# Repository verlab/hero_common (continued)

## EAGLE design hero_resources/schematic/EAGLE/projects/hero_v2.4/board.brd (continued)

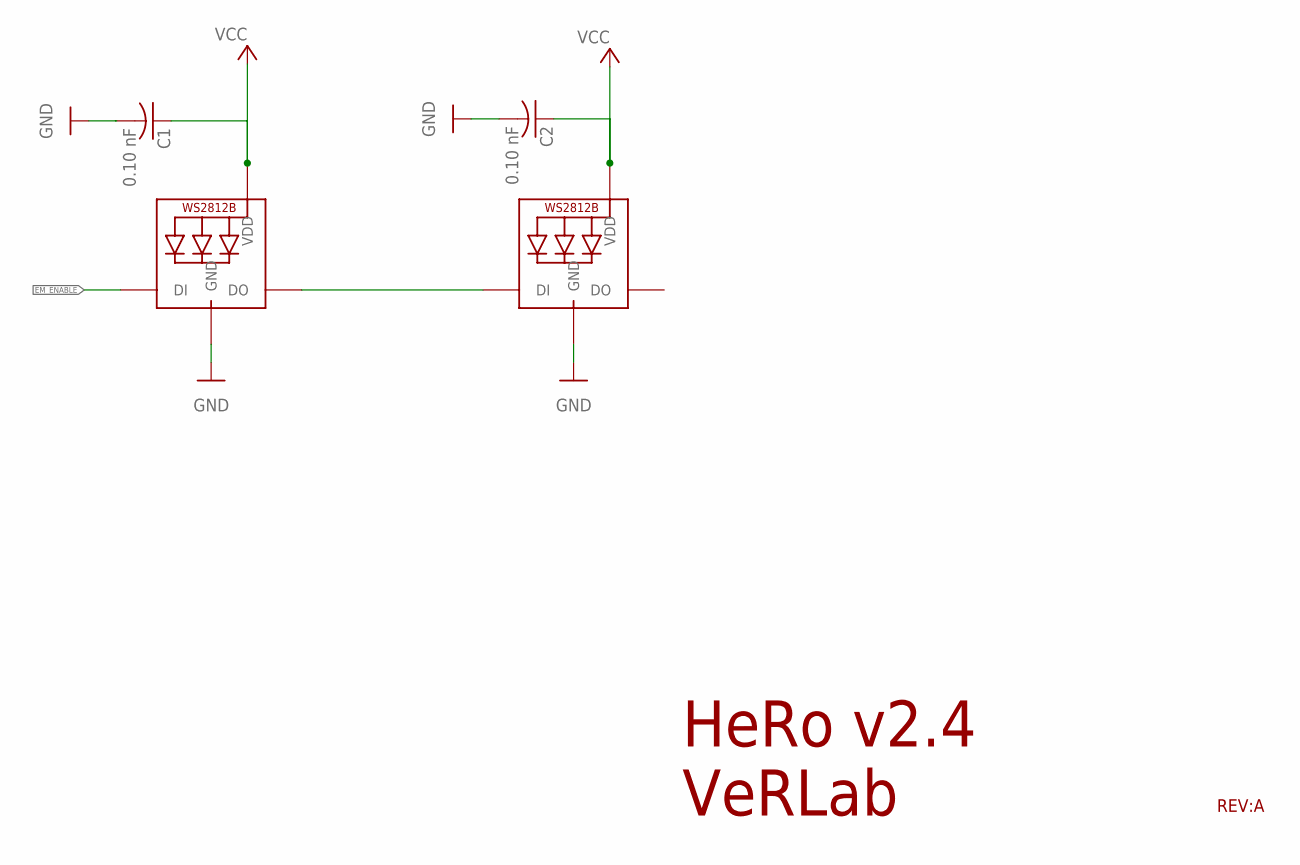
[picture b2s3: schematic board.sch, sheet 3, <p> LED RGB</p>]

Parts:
C1, C2: 0.10 nF; C0603
LED0, LED1: WS2812B5050; WS2812B

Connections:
EM_ENABLE: LED0.4-DIN (DI); also elsewhere on the board
GND: C1.2, C2.2, LED0.3-GND (GND), LED1.3-GND (GND); also elsewhere on the board
VCC: C1.1, C2.1, LED0.1-VDD (VDD), LED1.1-VDD (VDD); also elsewhere on the board
WS_OUT: LED0.2-DOUT (DO), LED1.4-DIN (DI)

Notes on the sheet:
HeRo v2.4 VeRLab
REV:A

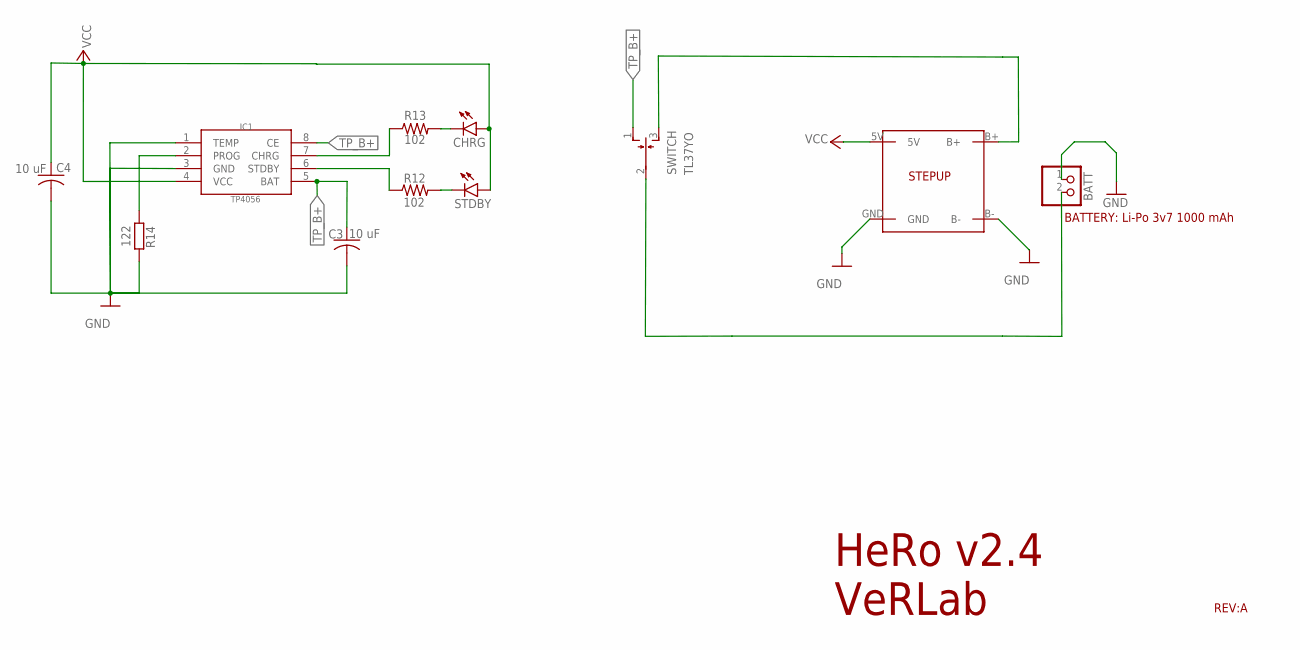
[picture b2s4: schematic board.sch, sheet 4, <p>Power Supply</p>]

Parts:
BATT: PINHD-1X2; 1X02
C3, C4: 10 uF; C0603
CHRG: LEDCHIP-LED0603; CHIP-LED0603
IC1: TP4056; SOP-8
OS1: STEPUP
R12, R13: 102; R0603
R14: 122; R0603
STDBY: LEDCHIP-LED0603; CHIP-LED0603
SWITCH: TL37YO; TL3XYO

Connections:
B+: OS1.B+, SWITCH.3 (S)
CHRG: IC1.7 (CHRG), R13.1
GND: BATT.1, C3.2, C4.2, IC1.1 (TEMP), IC1.3 (GND), OS1.B-, OS1.GND, R14.1; also elsewhere on the board
unnamed: CHRG.A, STDBY.A
unnamed: BATT.2, SWITCH.2
unnamed: CHRG.C, R13.2
unnamed: R12.2, STDBY.C
PROG: IC1.2 (PROG), R14.2
STDBY: IC1.6 (STDBY), R12.1
TP_B+: C3.1, IC1.5 (BAT), IC1.8 (CE), SWITCH.1 (O)
VCC: C4.1, IC1.4 (VCC), OS1.5V; also elsewhere on the board

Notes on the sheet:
HeRo v2.4 VeRLab
BATTERY: Li-Po 3v7 1000 mAh
REV:A

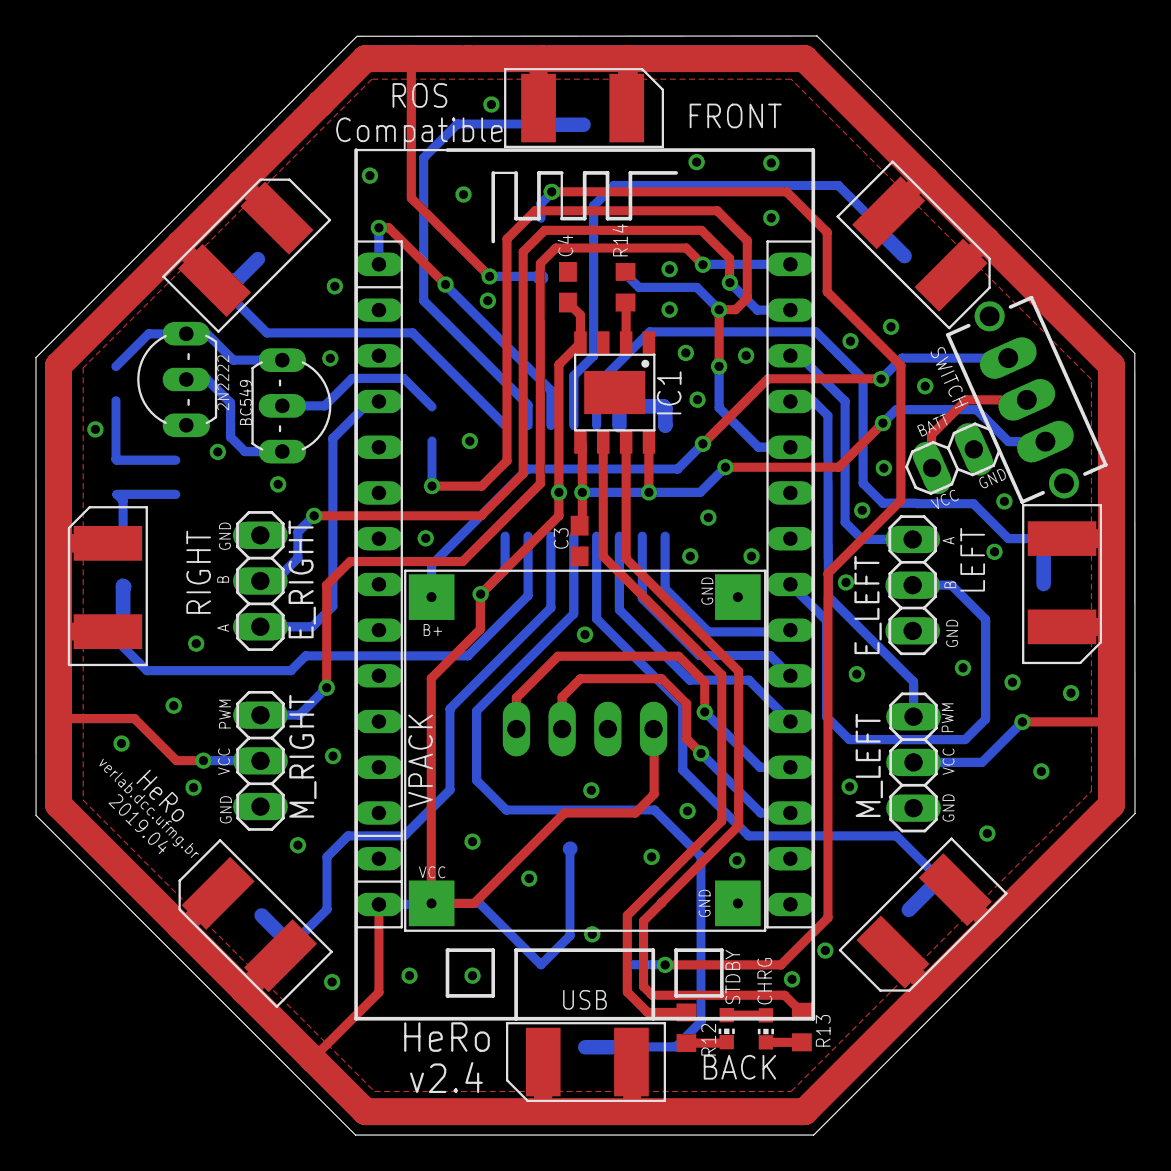
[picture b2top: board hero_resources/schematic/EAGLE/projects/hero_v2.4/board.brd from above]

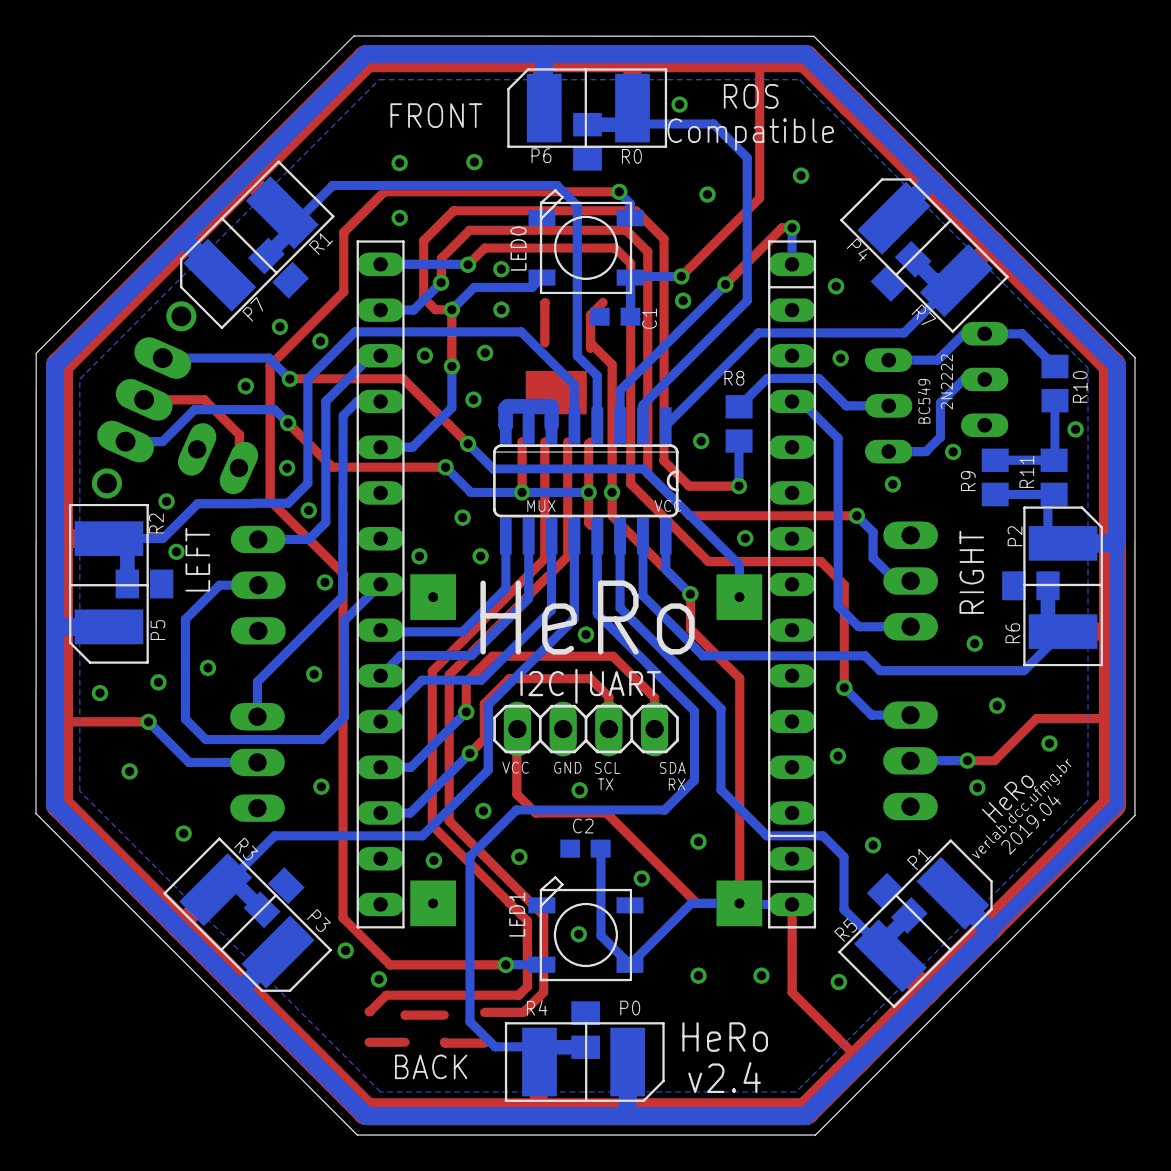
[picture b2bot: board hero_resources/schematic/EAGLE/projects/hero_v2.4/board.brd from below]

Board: 2 copper layers, 61.1 x 61.1 mm, 44 parts (18 on the bottom side), 38 nets.

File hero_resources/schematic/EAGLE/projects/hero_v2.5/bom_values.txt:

Partlist exported from /home/rezeck/EAGLE/projects/hero_v2.5/board.sch at 6/5/19 10:48 AM

Qty Value         Device         Package       Parts                            Description                  SPICEPREFIX
2                 LEDSML0805     SML0805       CHRG, STDBY                      LED                                     
1                 MOSFET-NREFLOW SOT23         IRLML2502                        N-Channel Mosfet                        
1                 PINHD-1X2      1X02          BATT                             PIN HEADER                              
4                 PINHD-1X3      1X03          E_LEFT, E_RIGHT, M_LEFT, M_RIGHT PIN HEADER                              
1                 PINHD-1X4      1X04          I2C|UART                         PIN HEADER                              
1                 STEPUP         STEPUP        OS1                                                                      
8                 TCRT5000       TCRT5000      P0, P1, P2, P3, P4, P5, P6, P7                                           
1   0 R           R-US_R0805     R0805         R9                               RESISTOR, American symbol    R          
2   0.10 nF       C-USC0603      C0603         C1, C2                           CAPACITOR, American symbol              
2   10 uF         C-USC0603      C0603         C3, C4                           CAPACITOR, American symbol              
2   102           R-EU_R0805     R0805         R12, R13                         RESISTOR, European symbol               
1   122           R-EU_R0603     R0603         R14                              RESISTOR, European symbol               
1   18 R          R-US_R0805     R0805         R10                              RESISTOR, American symbol    R          
1   4051D         4051D          SO16          IC2                              8-channel ANALOG MULTIPLEXER            
8   4k7           R-US_M0805     M0805         R0, R1, R2, R3, R4, R5, R6, R7   RESISTOR, American symbol               
1   4k7           R-US_R0805     R0805         R8                               RESISTOR, American symbol    R          
1   ESP12E_DEVKIT ESP12E_DEVKIT  ESP12E_DEVKIT U$1                              ESP12E DEVKIT BOARD                     
1   NM            R-US_R0805     R0805         R11                              RESISTOR, American symbol    R          
1   TL37YO        TL37YO         TL3XYO        SWITCH                           TINY SWITCH MOM OFF MOM                 
1   TP4056        TP4056         SOP-8         IC1                                                           X          
2   WS2812B5050   WS2812B5050    WS2812B       LED0, LED1

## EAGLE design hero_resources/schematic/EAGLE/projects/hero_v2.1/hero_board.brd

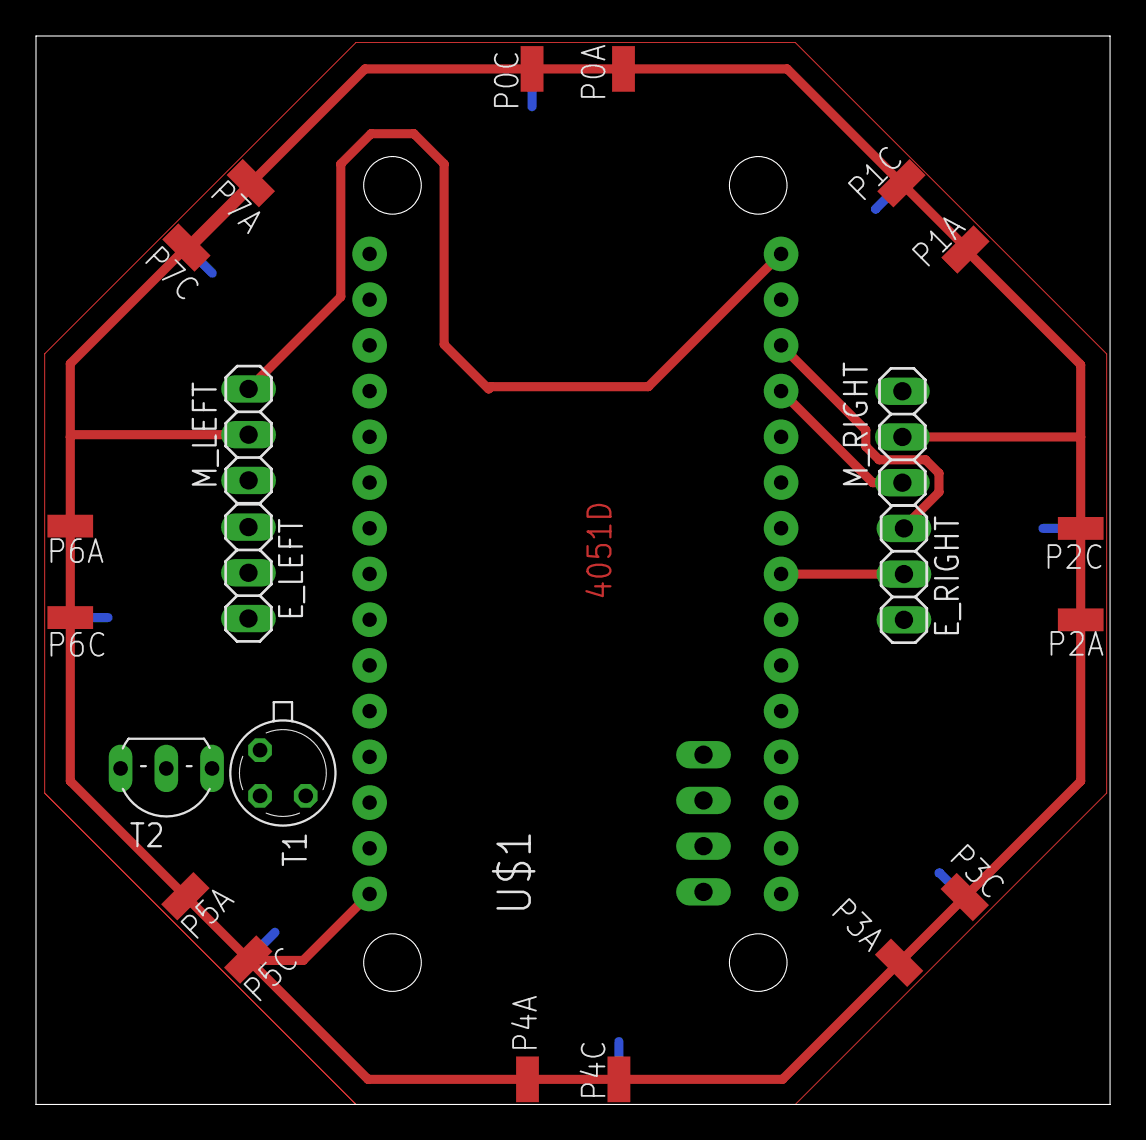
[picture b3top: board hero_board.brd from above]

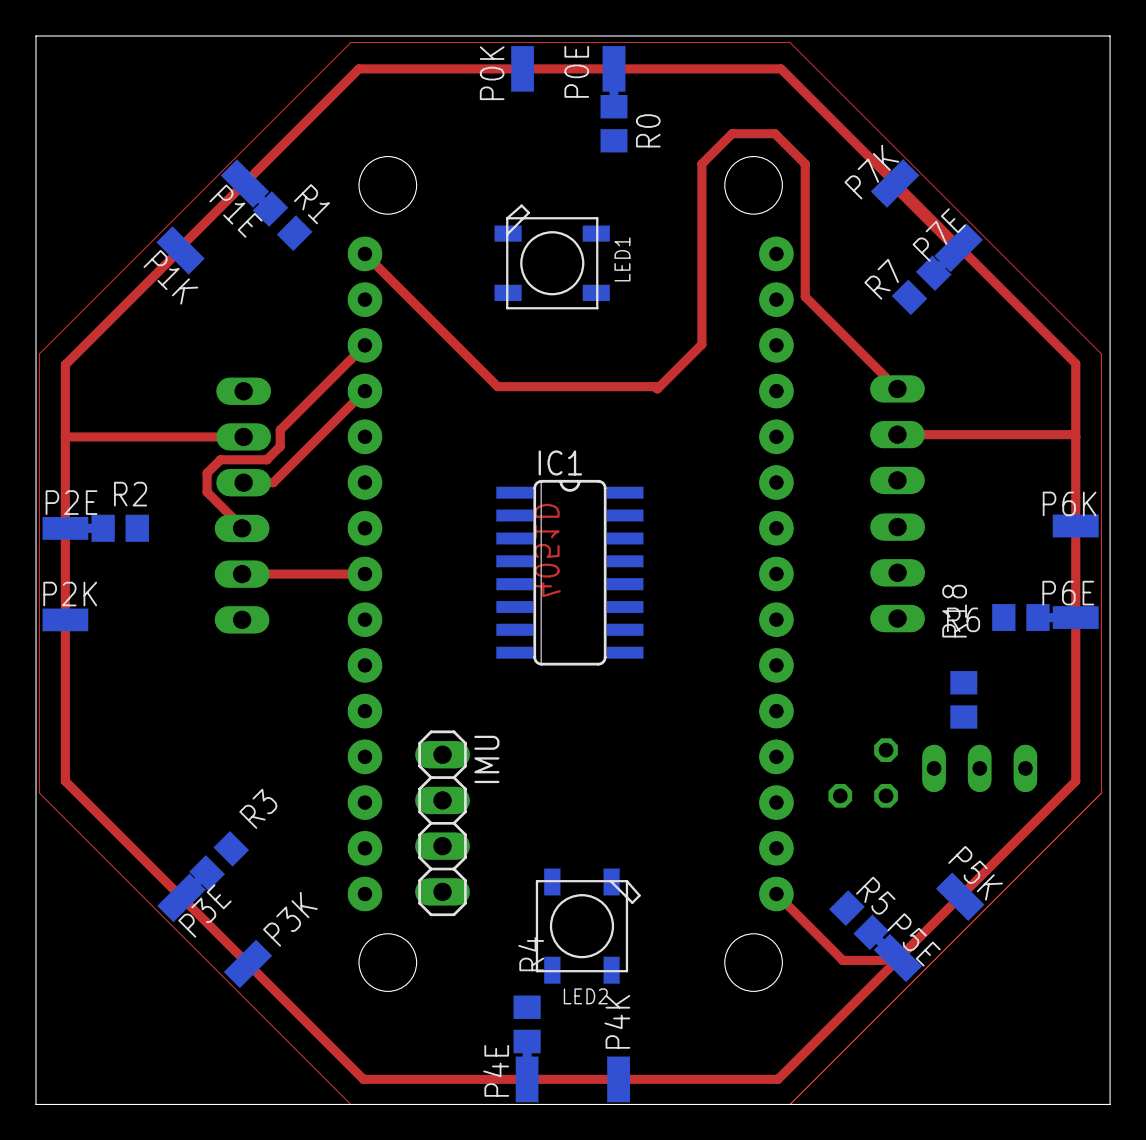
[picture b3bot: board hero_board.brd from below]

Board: 2 copper layers, 59.7 x 59.4 mm, 52 parts (29 on the bottom side), 27 nets.

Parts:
E_LEFT: 1X03
E_RIGHT: 1X03
IC1: 4051D; SO16
IMU: 1X04
LED1, LED2: WS2812B5050; WS2812B
M_LEFT: 1X03
M_RIGHT: 1X03
P0A, P0C, P0E, P0K, P1A, P1C, P1E, P1K, P2A, P2C, P2E, P2K, P3A, P3C, P3E, P3K, P4A, P4C, P4E, P4K, P5A, P5C, P5E, P5K, P6A, P6C, P6E, P6K, P7A, P7C, P7E, P7K: SMD1,27-2,54
R0, R1, R2, R3, R4, R5, R6, R7, R18: R0805
T1: 2N2222; TO18
T2: TO92-CBE
U$1: ESP12E_DEVKIT

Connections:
AD0: IC1.3, U$1.AD0
EM: P0K.1, P1K.1, P2K.1, P3K.1, P4K.1, P5K.1, P6K.1, P7K.1, R18.2
EM_ENABLE: LED1.4-DIN, T2.B, U$1.D4
E_LEFT_A: E_LEFT.3, U$1.SD3
E_LEFT_B: E_LEFT.2, U$1.D1
E_RIGHT_A: E_RIGHT.3, U$1.D2
E_RIGHT_B: E_RIGHT.2, U$1.D5
GND: E_LEFT.1, E_RIGHT.1, IC1.6, IC1.8, IMU.3, LED1.3-GND, LED2.3-GND, M_LEFT.1, M_RIGHT.1, R0.2, R1.2, R2.2, R3.2, R4.2, R5.2, R6.2, R7.2, T1.1, U$1.GND@1
MUX_A: IC1.11, U$1.D6
MUX_B: IC1.10, U$1.D7
MUX_C: IC1.9, U$1.D8
MUX_X0: IC1.13, P0E.1, R0.1
MUX_X1: IC1.14, P1E.1, R1.1
MUX_X2: IC1.15, P2E.1, R2.1
MUX_X3: IC1.12, P3E.1, R3.1
MUX_X4: IC1.1, P4E.1, R4.1
MUX_X5: IC1.5, P5E.1, R5.1
MUX_X6: IC1.2, P6E.1, R6.1
MUX_X7: IC1.4, P7E.1, R7.1
M_LEFT_PWM: M_LEFT.3, U$1.D0
M_RIGHT_PWM: M_RIGHT.3, U$1.D3
unnamed: T1.2, T2.E
unnamed: R18.1, T1.3, T2.C
unnamed: LED1.2-DOUT, LED2.4-DIN
SCL_TX: IMU.2, U$1.TX
SDA_RX: IMU.1, U$1.RX
VCC: IC1.16, IMU.4, LED1.1-VDD, LED2.1-VDD, M_LEFT.2, M_RIGHT.2, P0A.1, P0C.1, P1A.1, P1C.1, P2A.1, P2C.1, P3A.1, P3C.1, P4A.1, P4C.1, P5A.1, P5C.1, P6A.1, P6C.1, P7A.1, P7C.1, U$1.VIN

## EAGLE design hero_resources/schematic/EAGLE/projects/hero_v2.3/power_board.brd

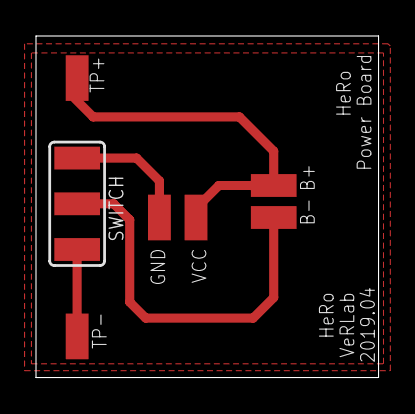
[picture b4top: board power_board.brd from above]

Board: 2 copper layers, 19.0 x 19.0 mm, 7 parts (0 on the bottom side), 4 nets.

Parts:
B+: SMD1,27-2,54
B-: SMD1,27-2,54
GND: SMD1,27-2,54
SWITCH: SJ_2W
TP+: SMD1,27-2,54
TP-: SMD1,27-2,54
VCC: SMD1,27-2,54

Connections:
unnamed: B-.1, SWITCH.2
unnamed: GND.1, SWITCH.1
unnamed: B+.1, TP+.1, VCC.1
unnamed: SWITCH.3, TP-.1

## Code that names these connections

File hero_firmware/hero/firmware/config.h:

/*
 ************************************************************************
 *  H E R O   F I R M W A R E
 ************************************************************************
 *
 * Paulo Rezeck <rezeck@dcc.ufmg.br>
 * Mauricio Ferrari <mauferrari@dcc.ufmg.br>
 * Hector Azpurua <hectorxxx@gmail.com>
 * 
 * HeRo Project
 * Computer Vision and Robotics Lab
 * Federal University of Minas Gerais - Brazil
 ************************************************************************/

#ifndef __CONFIG_H__
#define __CONFIG_H__

#define DEBUG 1


/* WIFI Config */
#define IP_A 10
#define IP_B 42
#define IP_C 0
#define IP_D 1
#define WIFI_SSID "epuck_net" // network name
#define WIFI_PASSWD "epuck_9895" // network password
#define ROS_MASTER_PORT 11411


/* Robot Params */
#define WHEEL_DIAMETER 4.955     /* Wheel diameter in cm. */
#define WHEEL_SEPARATION 6.335   /* Separation between wheels (cm) */
#define WHEEL_DISTANCE 0.06335   /* Distance between wheels in meters (axis length) */
#define WHEEL_CIRCUMFERENCE ((WHEEL_DIAMETER * M_PI)/100.0)  /* Wheel circumference (meters). */
#define MOT_STEP_DIST (WHEEL_CIRCUMFERENCE/288.0)  /* Distance for each motor step (meters); 
                                                      a complete turn is 288 steps (0.000535598 meters per step (m/steps)).

/* IO */
#define ENC_A_LEFT 14 // D2
#define ENC_B_LEFT 4 // D5
#define ENC_A_RIGHT 10 // SD3
#define ENC_B_RIGHT 5 // D1
#define MOTOR_RIGHT 16 // D3
#define MOTOR_LEFT 0 // D0
#define MUX_A 15 // D8
#define MUX_B 13 // D7
#define MUX_C 12 // D6
#define MUX_EN 2 // D4
#define I2C_SDA 3 // RX
#define I2C_SCL 1 // TX


/* WS2812b */
#define COLOR_SATURATION 255

/* MUX IR Control */
/* Analog Multiplexer 4051 */
//const int real_pos[8] = {0,1,2,5,6,7,4,3};
const int real_pos[8] = {0, 1, 2, 7, 3, 6, 4, 5};
// 0, 1, 2, 4, 6, 7, 5, 3

/* Control */
#define ENCODER_SPEED_GAIN 0.06
#define DEFAULT_KP 1200
#define DEFAULT_KI 7.5
#define DEFAULT_KD 3.5

#define MAX_BUFFER_SIZE 100

#endif  // ___CONFIG_H__

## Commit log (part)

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2017-03-08 Implemented differential control
2017-03-08 Renamed some files and disable robot to publish they ids
2017-03-09 Updated servo motor neutral position
2017-03-18 Added some info on README
2017-03-18 added cad file of robot
2017-03-18 fix line
2017-03-20 Rename launch and change neutral position of the wheels.
2017-03-20 Update servo neutral position
2017-03-20 Created teleop launch to control via keyboard the robots
2017-03-20 Adjust to use microseconds write on servo
2017-03-22 Implemented sender mode on robots
2017-03-23 Remove submodule entry
2017-03-23 Added RF24 library modified.
2017-03-23 Implement mode to automatic find the enable robots in environment.
2017-03-24 Implement mode to (simutaneous) receive data from Sensors and control the robot.
2017-04-05 Set all read pipes with the same address
2017-04-05 Set teleop launch to control a specific robot
2017-04-13 Create WifiHardware to comunicate via wifi with ros using nodemcu device
2017-04-14 Create a new messages types and implement robot firmware based on ROS
2017-04-17 Removed sensitive data from file
2017-05-26 Add IR sensor
2017-05-27 Simplified arduino code, added twist messages, simple config in main cpp file
2017-05-27 added new control algo simplified some functions, need some more testing
2017-05-30 reverted old control algo
2017-05-30 added camera and tracker launch file
2017-05-30 added camera parameters in file
2017-05-30 Added calibration file from arena
2017-05-30 Added markers folder, and tracker script to make the robot follow a goal marker.
2017-05-30 updated track launch file
2017-05-30 updated tracker software and a simple random walker for the nodemcu firmware
2017-05-31 updated camera launch
2017-06-01 added serial node, modified to accept different ports
2017-06-02 Added common markers
2017-06-05 Add into firmware the parameter of the second robot, added potential field control.
2017-06-05 Added tracker, firmware parameters, markers
2017-06-07 Update README.md
    Describing HeRo setup.
2017-06-07 Rename package
2018-04-17 added nodemcu firmware with a friendly EEPROM editor
2018-05-04 Added 3d printer parts
2018-05-04 Added nodemcu and jst pin 3d model
2018-05-04 Added tcrt5000 3d model
2018-08-21 Added new cad model
2018-09-26 Add description and simulation on gazebo
2018-09-27 Added laser and multi hero launch
2018-10-02 Improved collision, inertial and modularization
2018-10-02 Fix laser noise and differential controller plugin
2018-10-02 Added populations cardbox
2018-10-02 Added set of examples to control hero; added blink controller and potential field controller for local navigation.
2018-10-02 Added gazebo images and hero rendered
2018-10-03 Added call for rosserial tcp server into hero bringup; Teleop using keyboard it's also include.
2018-10-05 Added Gazebo ros graph image
2018-10-05 Added some test to hero firmware
2018-10-20 Added support to ar track alvar to provide global pose to HeRo; Not tested yet.
2018-10-24 Update odometry_test
2018-10-24 Added odometry test; hero compare to epuck.
2019-01-15 Added IR, IMU and Encoders tests
2019-01-15 Update firmware with IMU, Encoders, IR and LEDs
2019-01-15 Added cad and board schematic
2019-01-28 Added new 3d model; update tests; refactor sketches
2019-04-17 Remove verbose of gazebo launch and update gazebo world with real time
2019-04-17 Update PCB schematic; Version 2.5 not tested yet.
2019-04-22 Fix battery connector position in board v2.5
2019-04-24 Fix unset interruption mode to the GPIO10; Check if the esp8266 is on DIO Flash mode.
2019-04-24 Fix board v2.5 charge power led to 0805.
2019-04-28 Added new message types for encoder and motor; update setPID service;
2019-04-28 Update firmware to version 2.5; refactored the firmware; added webpage setup wifi; fix encoder read interruption; fix PID parameters
2019-04-28 Added picture resource
2019-06-03 Added builded binary code
2019-06-03 Remove PID library
2019-06-03 Fix PID library
2019-06-05 Added hero v2.5 board BOM
2019-12-12 Fix neopixel test delay
2020-01-17 Added ir and neopixel test; enable rosserial server to fork.
2020-01-17 Fix wifi setup.
2020-01-23 Fix some issues in these test; Add ir and neopixel test
2020-01-25 Added mosfet datasheet
2020-01-29 updating the list of ROS package dependeces
2020-01-29 updating how to install information
2020-01-29 add the arduino IDE download link
2020-01-30 Fix ROS package dependencies; Add hero_firware as ROS package; Add N025P datasheet.
2020-02-08 Update ros library; Update neopixel, ir and motor tests
2021-02-04 Improve gazebo simulation setup; add swarm arena setup;
2021-02-07 Change simulation parameters
2021-07-15 updating 3d model parts
2022-04-13 Major Modifications
2022-04-14 Remove ar-track-alvar dependencies
2022-04-14 remove ar-track dependencies
2022-04-14 Update to use urdf instead xacro -- fix ros noetic version
2022-04-19 Update eagle projects; BOM available
2022-04-19 Update BOM; TP4056 Optional
2022-04-20 Add last CAD model
2022-04-21 Fix castor wheel 3d printer stl
2022-04-21 Fix motor gear 3d printer file
2022-04-26 Set theme jekyll-theme-slate
2022-04-27 Rename _layouts.md to _layouts/defaults.md
2022-04-27 Rename defaults.md to default.html
2022-05-01 Setup new gh-pages
2022-05-03 Delete default.html
    Delete default.html because it was the old home page
2022-05-04 Add feature save launch file name dialog for hero wizard
2022-05-16 Add swtich key datasheet
2022-05-17 Update datasheet links
2022-05-17 Fix Header Responsivity
2022-05-18 Add assembly_table.pdf
2022-05-19 Update Materials
2022-05-25 Add file assembly_materials.pdf
2022-06-13 Created rgbscreen.py
2022-06-14 commit changes
2022-06-14 New pages added
2022-06-14 Fix pcb_order nav-bar
2022-06-15 Update hero_resources
2022-06-15 Major Update
2022-06-16 Add castor wheel and wheel assembly tutorial
2022-06-16 Remove assembly tutorial title
2022-06-16 add rivet to material list
2022-06-16 Update material list
2022-09-07 Adding docker files
2022-09-07 Fix shebang python3
2022-09-07 Fix shebang for python3; Add wizard gui images
2022-09-07 Fix package dependecies list
2022-09-07 Add docker file; fix dependencies list
2022-09-07 Launch ROS1 container
2022-09-07 Launch ROS1 container example
2022-10-09 Update PCB to support MT3608 stepup
2023-01-05 Fix resistors (builtin charge) wrong description
2023-01-05 Fix builtin recharger resistor wrong description #16
2023-01-07 Fix IRAM_ATTR problem with interrupts on ESP8266; Encoder Lib v1.4.3; issue #15
2023-01-07 Fix i2s.h missing issue for NeoPixelBus, esp8266 board > 2.5.0-3.1.0; issue #14
2023-01-07 Update firmware version
2023-01-08 Fix Encoder Lib absence of interrupt on gpio 10
2023-01-08 Fix tf name for laser frame
2023-01-09 Fix MOSFET pinMode reset for IR sensors
2023-02-09 Fix constant parameter
2023-02-09 Fix robot urdf compatibility
2023-02-09 Update robot config params
2023-02-13 Fix rviz config file
2023-02-13 Update firmware config file and fix bug IR sensor
2023-02-13 Add IR calibration script #17
2023-02-13 Add IR Calibration Support 3D printer #17
2023-02-13 Fix xacro urdf remapping #18, thanks @jacobh2299
2023-03-06 Fix incorrectlu battery connector polarity labeled on PCB #19
2023-07-27 Add random walk demo to firmware
2023-07-27 Fix docker launch script image name
2023-07-27 Update range sensor example
2023-08-10 Add IR calibration script
2023-08-10 Fix IR overdriver and signal to meter function
2023-08-10 Update launch file
2023-08-12 Update robot description in launch file
2023-08-12 Fix rosserial flushoutput and add rqt
2023-08-14 Update frame name for compability with noetic
2023-08-14 Add calibration script
2023-08-26 Update docker launch script
2023-08-26 Decrease motor stiffness param
2023-09-02 Update pcb board version
2023-09-02 Update firmware
2023-09-02 Update docker and launch files
2023-09-06 Fix hero gazebo wizard ui size constraint
2023-09-13 Fix the tf part of the launch file generation script
2023-09-14 Update dockerfile
2023-09-20 Add new arena environments and maps
2023-09-20 Add map server for simulated arenas
2023-09-22 Fix map z origin to match with arena floor
2023-09-22 Update hero laser description to match with real robots
2023-09-22 Remove unecessary file
2023-09-23 Fix map undesired rotation param
2023-09-23 Reduce mesh polygon to improve gazebo performance
2023-09-24 Reduce model polygons to increase simulation performance
2023-09-25 Changing from alvartrack to apriltag camera tracker
2023-10-02 Fix unindent typo issue
2023-10-03 Add script to convert tag pose information to robot odometry
2023-10-08 Update camera calibration parameters
2023-10-08 Decrease hero simulation update rate
2023-10-08 Fix unmatching PCB board version 2.7 (issue #22)
2023-10-08 Update pcb_order.md
    Fix link for wrong gerber pcb version
2023-10-16 local planner topics name correction
2023-10-23 Add catkin build tools
2024-02-24 Update hero tracker configuration
2024-02-24 Add tag to pose converter and filter
2024-02-24 Add localization filter and update rviz config
2024-02-24 Add laser enable/disable ros topics
2024-02-24 Update gazebo sim parameters
2024-02-24 Update ros1 docker launch script
2026-05-04 Add initial PlatformIO configuration and web configuration files for HERO firmware
    - Created .gitignore to exclude build artifacts and IDE files.
    - Added platformio.ini for managing project dependencies and build settings.
    - Updated config.h with new versioning and motor ramp parameters.
    - Enhanced IMUSensor and MotorDriver classes for web configuration support.
    - Introduced web_config_embed files for offline web UI.
    - Implemented LEDStatus and WheelEncoder updates for web integration.
2026-05-07 Update firmware version and enhance web configuration
    - Updated FIRMWARE_VERSION to "v3.11" in config.h.
    - Improved comments for proximity sensor calibration indices in config.h.
    - Refactored web configuration HTML for clarity, including renaming tabs and headers for better user experience.
    - Adjusted API telemetry handling in WebConfig.ino to utilize new laser scan slot angle order for IR sensor data processing.
2026-06-11 Enhance motor control initialization and configuration
    - Updated motor pin definitions in config.h for clarity on GPIO usage.
    - Introduced MotorPinsEarlyInit struct in firmware.ino to ensure motor pins are set to LOW before global constructors run.
    - Added drivePinsSafe method in MotorDriver class to safely set motor pins to LOW after detaching servos.
    - Increased maximum ramp rate in config.h from 8000 to 20000 for improved motor control.
    - Adjusted web configuration input limits for motor ramp settings to reflect new maximum.
